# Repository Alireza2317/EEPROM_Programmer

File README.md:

# Arduino EEPROM Programmer (28C16)

A custom PCB shield and Arduino firmware designed to program **28C16 Parallel EEPROMs**.

This tool is essential for projects like the **Ben Eater 8-bit computer**, allowing you to burn microcode or 7-segment display logic into non-volatile memory without manually toggling dip switches.

## 🔌 Hardware Design (KiCad)
The `gerbers/` and root directory contain the full design files for a custom PCB that fits on top of an Arduino (or connects via headers).

* **Chip Support:** 28C16 (2K x 8-bit Parallel EEPROM).
* **Design Tool:** KiCad (Schematic & PCB files included).
* **Status:** Production-ready Gerber files are available in the `gerbers` folder.

### 📸 PCB Preview

## 💻 Firmware (Arduino)
The C++ code in `arduino_programmer/` handles the write cycle timing and address management.

### Key Features
* **Write Cycle Control:** Manages the Write Enable (WE) and Chip Enable (CE) pulses required by the 28C16 datasheet.
* **7-Segment Decoding:** By default, the code includes a lookup table to program the EEPROM with hexadecimal digits (0-9) for a common-cathode 7-segment display.
* **Customizable:** You can modify the `data` array to burn any microcode instruction set.

## 🚀 Getting Started

### 1. Fabrication / Wiring
You can either:
* **Order the PCB:** upload the zip gerber files to a PCB manufacturer (JLCPCB, PCBWay, etc.).
* **Breadboard it:** Follow the pinout defined in the `arduino_programmer.ino` file to wire the EEPROM directly to the Arduino digital pins.

### 2. Flashing
1.  Open `arduino_programmer/arduino_programmer.ino` in the Arduino IDE.
2.  Connect your Arduino.
3.  **Verify the pin definitions** at the top of the file match your wiring.
4.  Upload the sketch.
5.  Open the **Serial Monitor** (57600 baud) to see the programming status.

## ⚠️ Important Notes

* **Timing:** The 28C16 requires a specific write pulse width (usually < 1ms). The code handles this, but check your specific datasheet if using a different variant (e.g., 28C64).

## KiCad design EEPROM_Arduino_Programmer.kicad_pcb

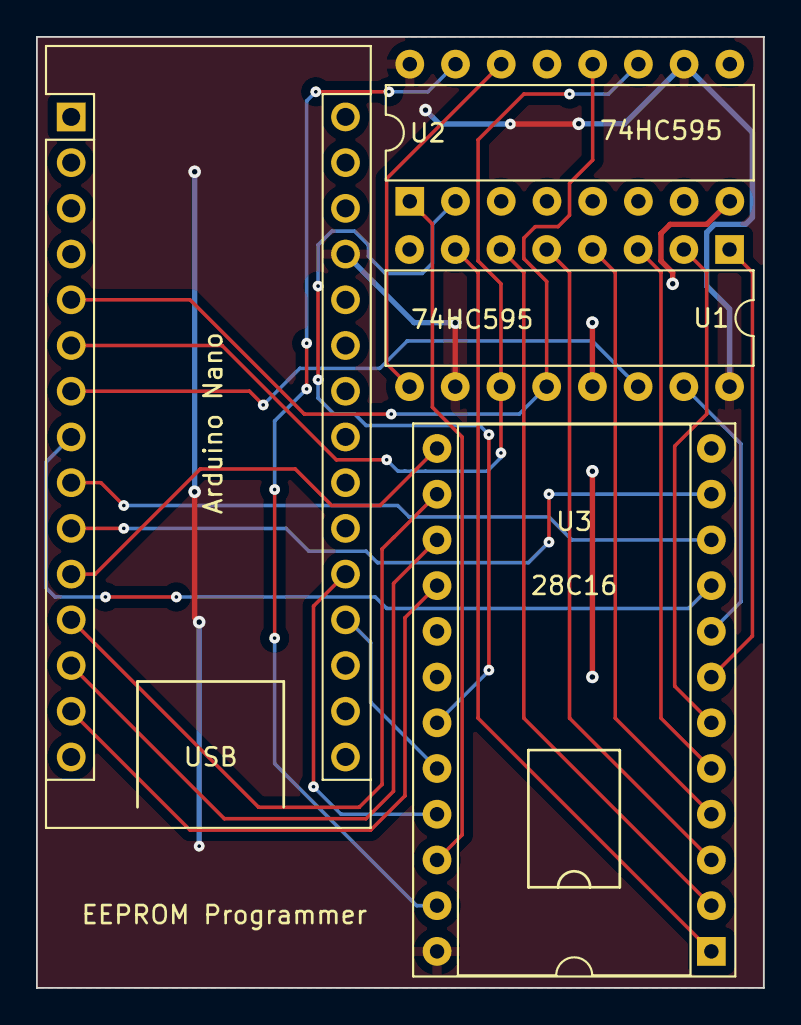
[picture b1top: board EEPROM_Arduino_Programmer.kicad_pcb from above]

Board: 2 copper layers, 40.4 x 52.8 mm, 4 parts (0 on the bottom side), 26 nets.

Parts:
Arduino Nano: Arduino_Nano_v2.x; Arduino_Nano
U1, U2: 74HC595; DIP-16_W7.62mm
U3: 28C16_EEPROM; DIP-24_W15.24mm_Socket

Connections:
/A0: U1.15 (QA), U3.8 (A0)
/A1: U1.1 (QB), U3.7 (A1)
/A2: U1.2 (QC), U3.6 (A2)
/A3: U1.3 (QD), U3.5 (A3)
/A4: U1.4 (QE), U3.4 (A4)
/A5: U1.5 (QF), U3.3 (A5)
/A6: U1.6 (QG), U3.2 (A6)
/A7: U1.7 (QH), U3.1 (A7)
/A8: U2.15 (QA), U3.23 (A8)
/A9: U2.1 (QB), U3.22 (A9)
/A10: U2.2 (QC), U3.19 (A10)
/D0: Arduino Nano.8 (D5), U3.9 (I/O0)
/D1: Arduino Nano.9 (D6), U3.10 (I/O1)
/D2: Arduino Nano.10 (D7), U3.11 (I/O2)
/D3: Arduino Nano.11 (D8), U3.13 (I/O3)
/D4: Arduino Nano.12 (D9), U3.14 (I/O4)
/D5: Arduino Nano.13 (D10), U3.15 (I/O5)
/D6: Arduino Nano.14 (D11), U3.16 (I/O6)
/clk: Arduino Nano.5 (D2), U1.12 (RCLK), U2.12 (RCLK)
/data: Arduino Nano.7 (D4), U1.14 (SER)
/latch: Arduino Nano.6 (D3), U1.11 (SRCLK), U2.11 (SRCLK)
/~OE: Arduino Nano.19 (A0), U3.20 (~OE)
/~WE: Arduino Nano.20 (A1), U3.21 (~WE)
GND: Arduino Nano.4 (GND), Arduino Nano.29 (GND), U1.8 (GND), U1.13 (~OE), U2.8 (GND), U2.13 (~OE), U3.12 (GND), U3.18 (~CE)
unnamed: U1.9 (QH'), U2.14 (SER)
VCC: Arduino Nano.27 (+5V), U1.10 (~SRCLR), U1.16 (VCC), U2.10 (~SRCLR), U2.16 (VCC), U3.24 (VCC)

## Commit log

2022-05-22 created schematic & pcb in kicad and arduino code arduino code programs the chip for seven segment displays by default
2022-05-22 updated arduino code
2022-05-22 added .gitignore
2025-12-07 updated .gitignore
2025-12-07 updated kicad version from 7 to 9!
2025-12-07 updated gerber files
2025-12-07 update pcb

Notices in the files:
README.md:
License: CC0 1.0
